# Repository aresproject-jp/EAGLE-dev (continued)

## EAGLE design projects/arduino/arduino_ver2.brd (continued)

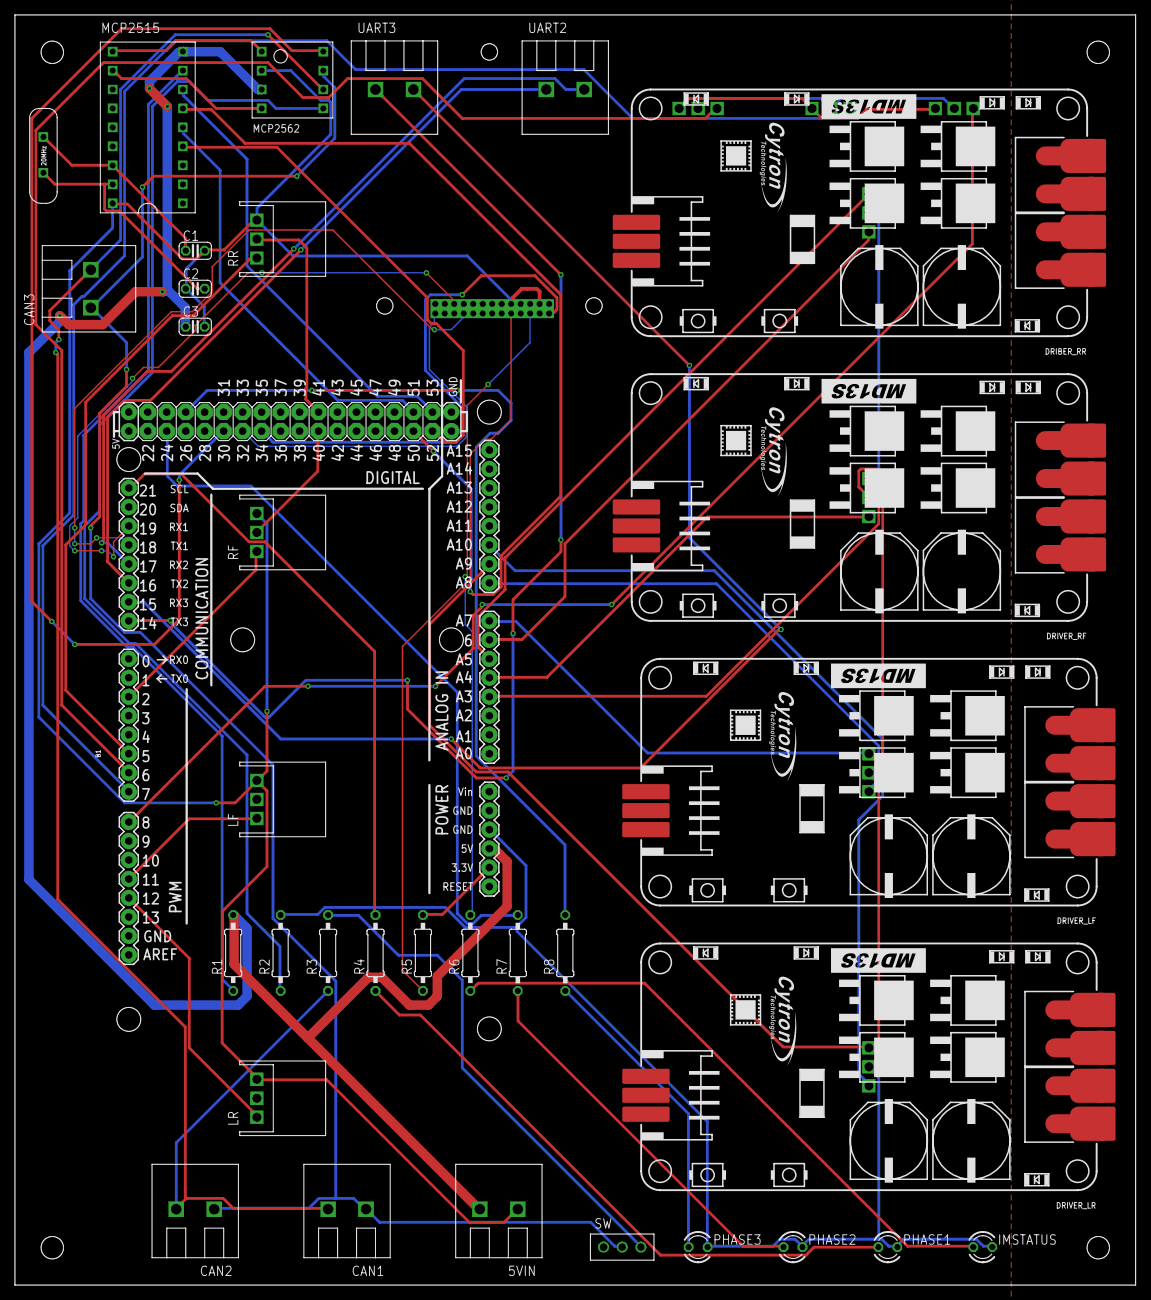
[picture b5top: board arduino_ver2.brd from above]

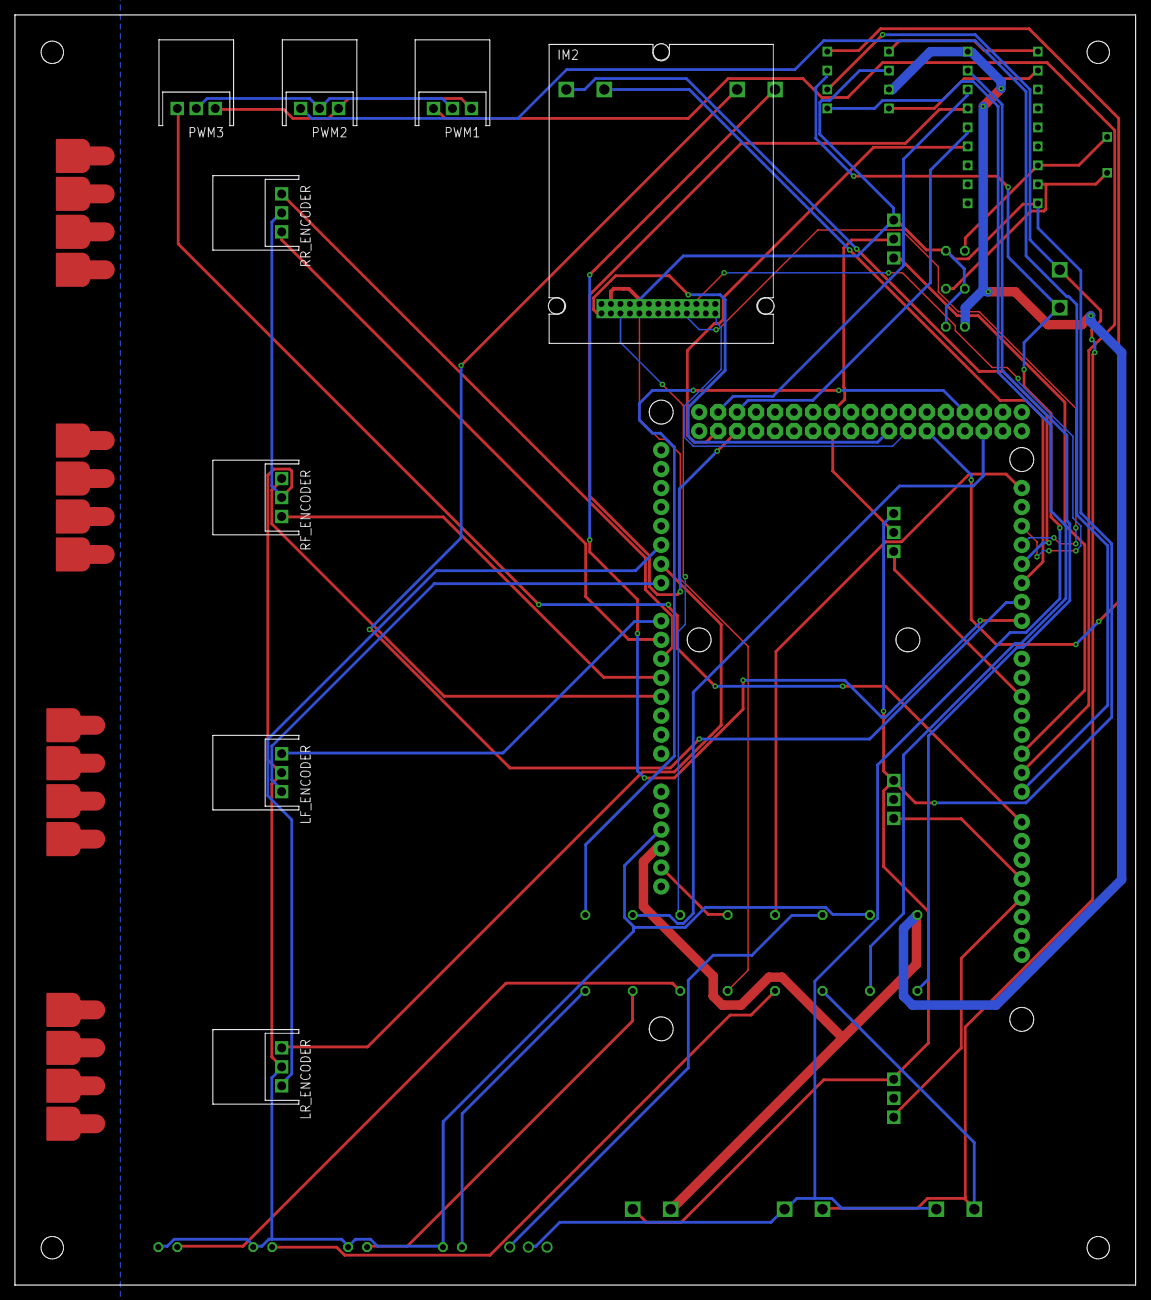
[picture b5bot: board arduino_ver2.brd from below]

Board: 2 copper layers, 150.0 x 170.0 mm, 42 parts (8 on the bottom side), 54 nets.

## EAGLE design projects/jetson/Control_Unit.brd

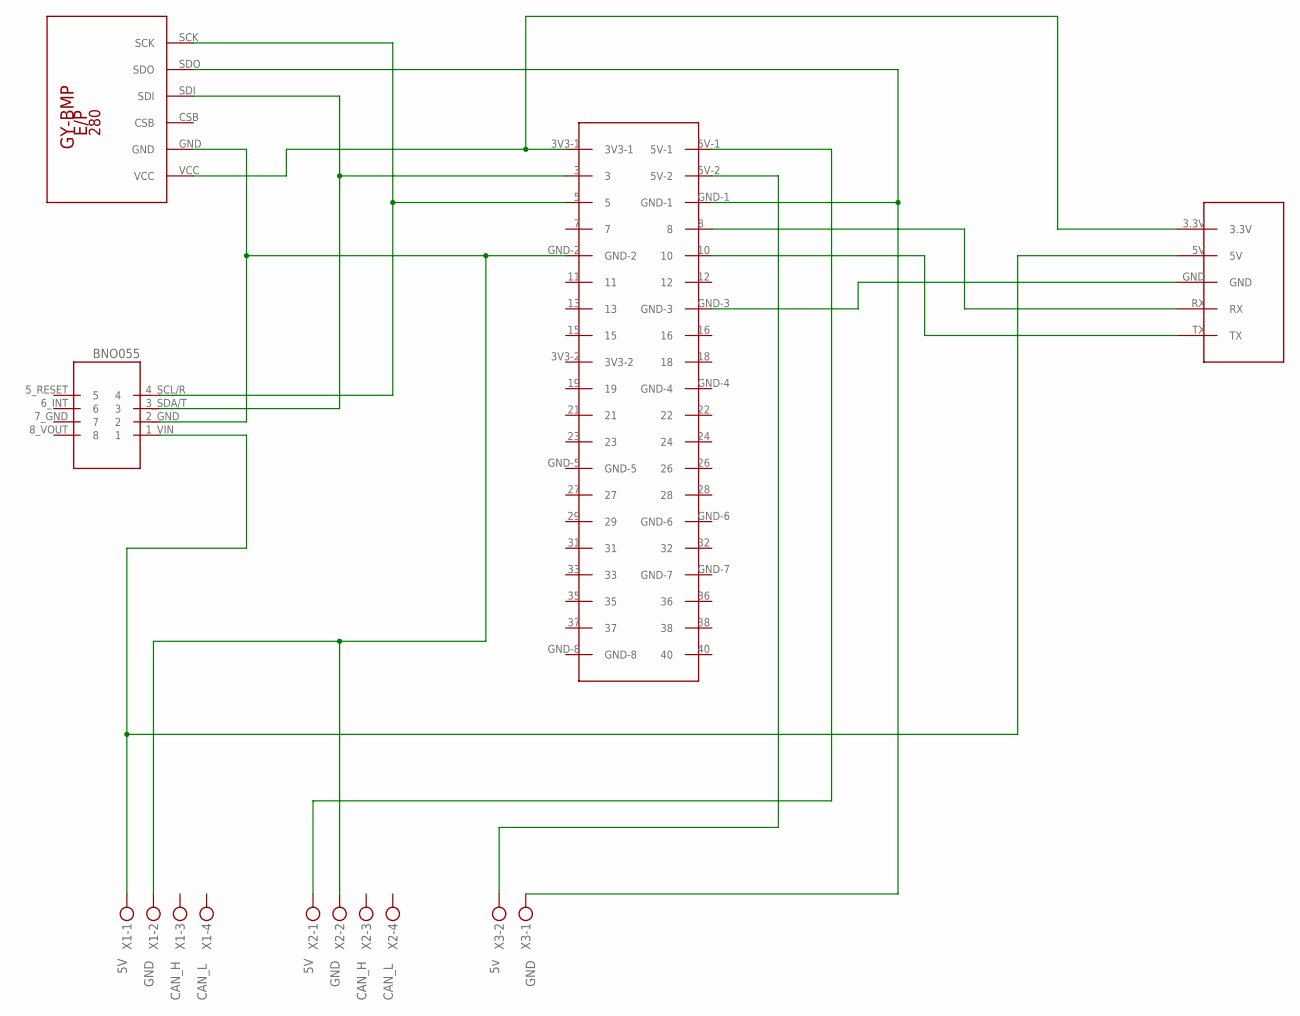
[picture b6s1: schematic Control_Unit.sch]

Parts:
JN1: JETSON_NANO
U$1: GY-BPM280; GY-BMP280-FOOTPRINT
U$2: BNO055
U$3: WIRELESS_PINS
X1, X2: MKDSN1,5/4-5,08
X3: MKDSN1,5/2-5,08

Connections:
unnamed: JN1.3V3-1, U$1.VCC, U$3.3.3V
unnamed: JN1.GND-2, U$1.GND, U$2.2_GND (2), X1.2, X2.2
unnamed: JN1.GND-1, U$1.SDO, X3.1
unnamed: JN1.3, U$1.SDI, U$2.3_SDA/T (3)
unnamed: JN1.5, U$1.SCK, U$2.4_SCL/R (4)
unnamed: U$2.1_VIN (1), U$3.5V, X1.1
unnamed: JN1.GND-3, U$3.GND
unnamed: JN1.5V-1, X2.1
unnamed: JN1.8, U$3.RX
unnamed: JN1.10, U$3.TX
unnamed: JN1.5V-2, X3.2

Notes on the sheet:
GND
CAN_H
CAN_L

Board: 2 copper layers, 7 parts (0 on the bottom side), 11 nets, no tracks yet.

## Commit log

2022-12-24 update_kato
2022-12-24 kato
2022-12-25 changed
2022-12-28 chenged discription
2022-12-28 change description
2022-12-29 modifed user name
2022-12-31 add lib
2023-01-01 changed husg20
2023-01-02 add module_MCP2515
2023-01-03 update power
2023-01-05 create arduino
2023-01-08 Modify BNO055
2023-01-09 Copied BMP280 Library
2023-01-09 Create Control Unit sch, brd (not finished yet)
2023-01-09 update control unit sch, brd
2023-01-10 update cad
2023-01-10 Add GPS lbr (thanks to Kota)
2023-01-10 Create Jetson board
2023-01-10 NISHIMOTO_TAKENORI
2023-01-11 modify jetson nano and Arduino board
2023-01-11 create jetson without CAN
2023-01-12 changeArduino
2023-01-12 change all
2023-01-17 power
2023-01-18 arduino
2023-01-18 anya
2023-01-20 Place hole in Jetson board
2023-01-20 Autoroute Jetson Board
2023-01-21 wakuwaku
2023-01-22 Resize Jetson Board
2023-01-22 finish
2023-03-03 Create Jetson Nano.pdf
    KATOONAMI
